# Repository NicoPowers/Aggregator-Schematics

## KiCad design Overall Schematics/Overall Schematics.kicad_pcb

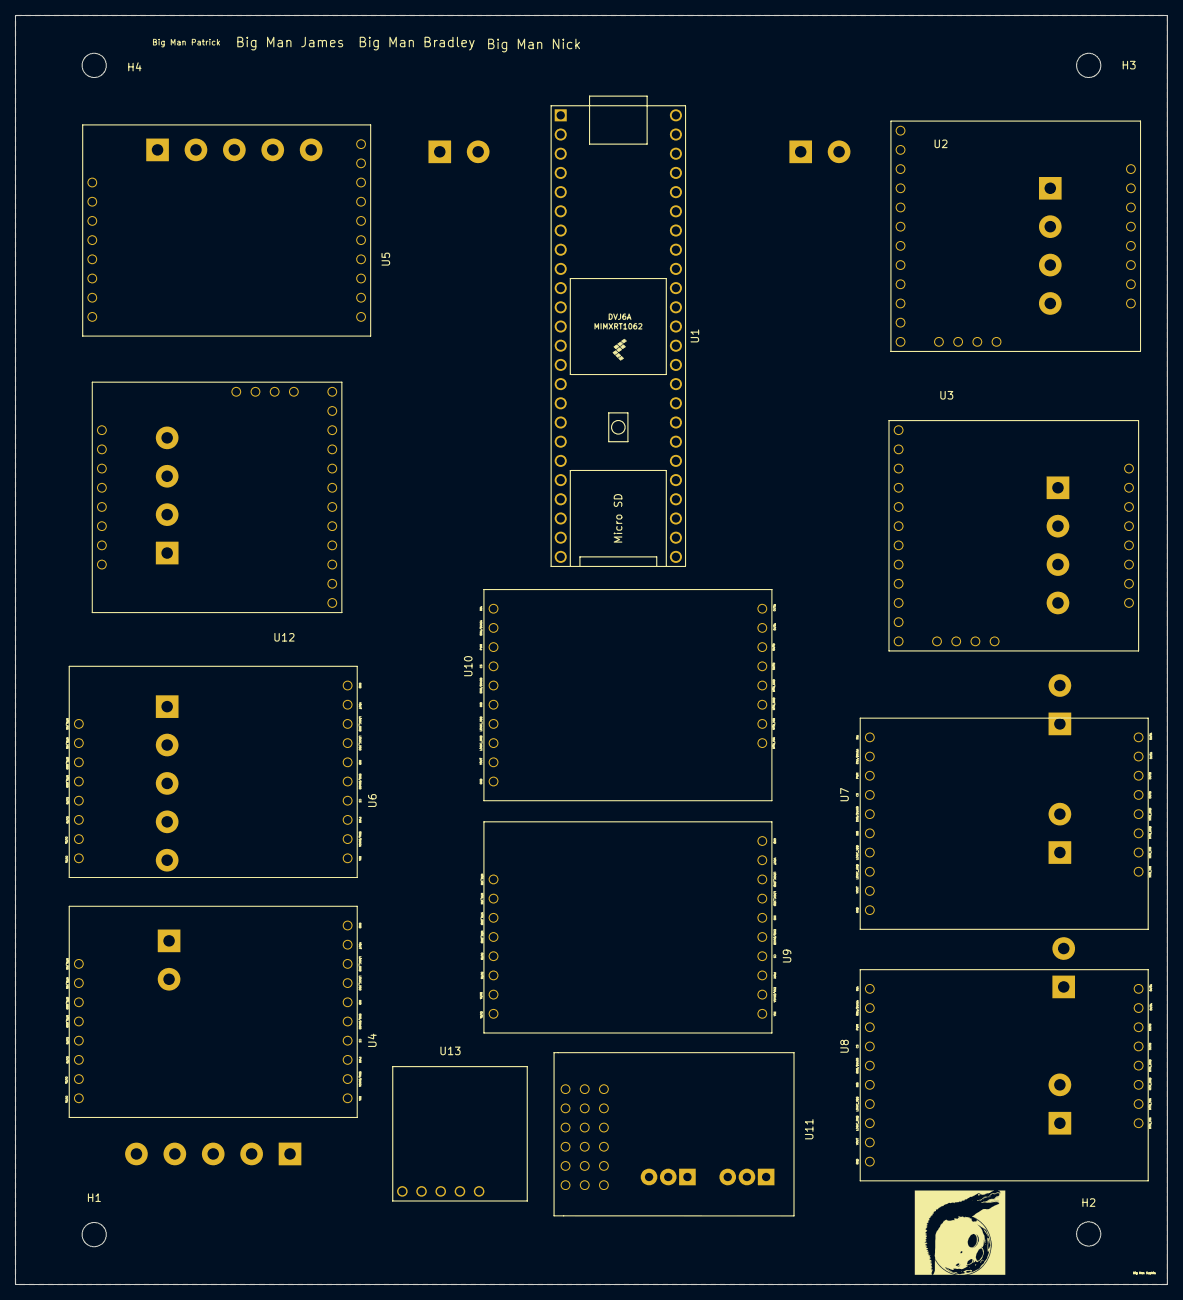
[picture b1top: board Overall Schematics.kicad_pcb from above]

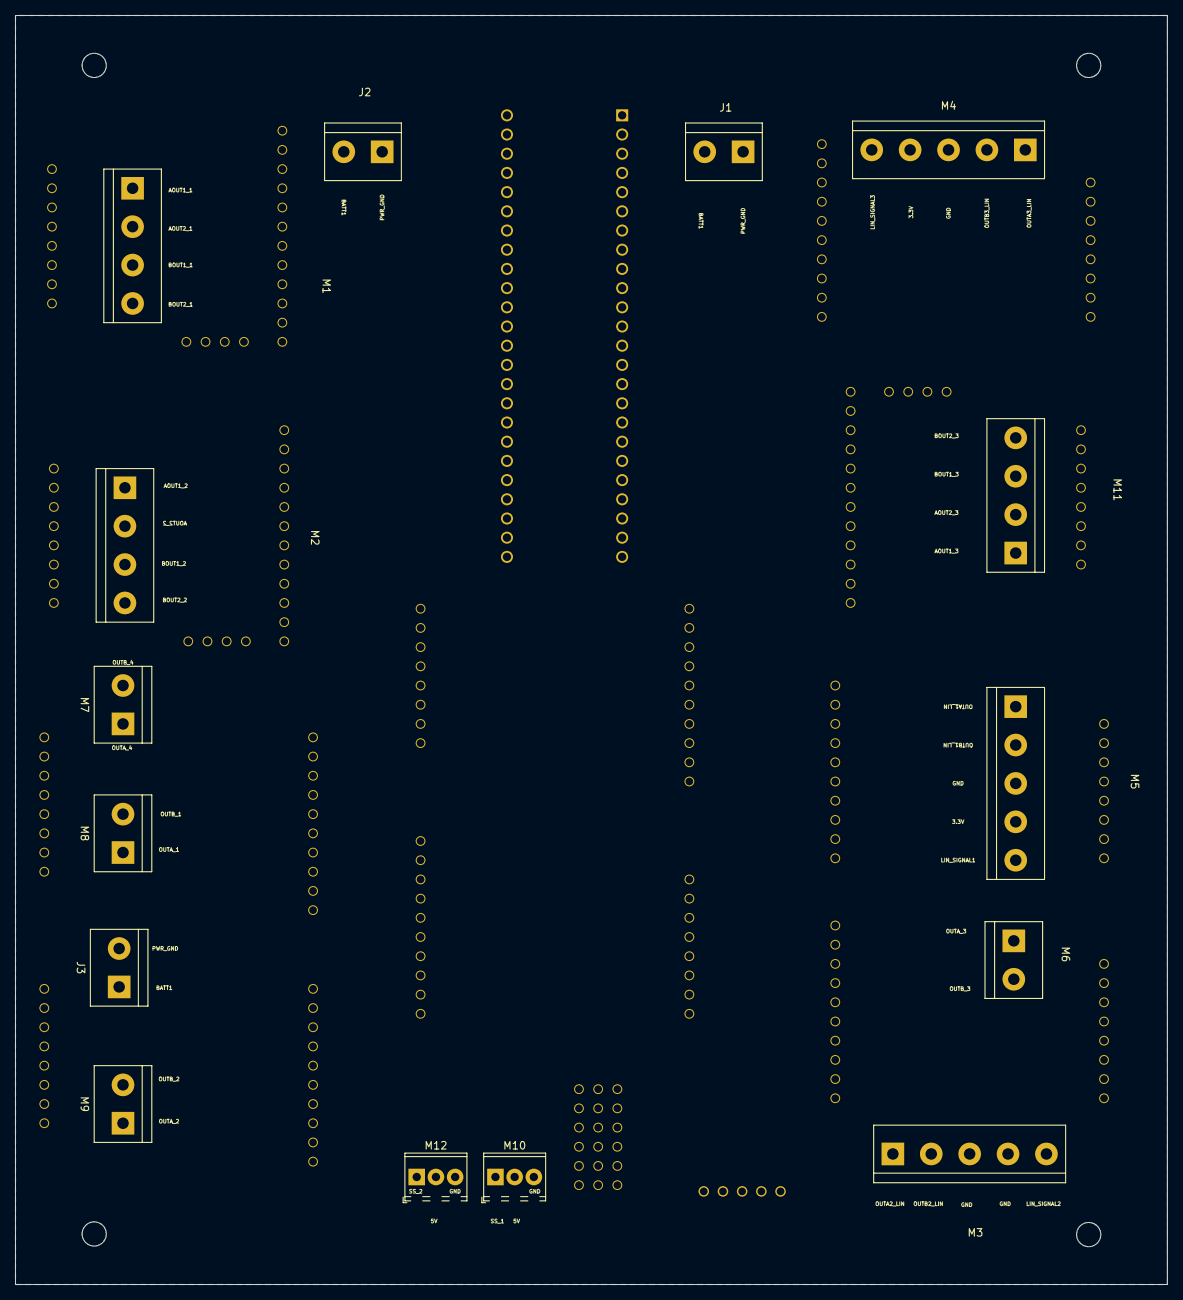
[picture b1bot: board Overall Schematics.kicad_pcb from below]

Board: 2 copper layers, 152.4 x 167.9 mm, 32 parts (15 on the bottom side), 67 nets, no tracks yet.

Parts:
H1, H2, H3, H4: MountingHole; MountingHole_3.2mm_M3
J1: WattMeter1_Output; TerminalBlock_bornier-2_P5.08mm
J2: WattMeter2_Output; TerminalBlock_bornier-2_P5.08mm
J3: Intel_Buck_Converter_Input; TerminalBlock_bornier-2_P5.08mm
M1, M2, M11: Stepper_Motor_bipolar; TerminalBlock_bornier-4_P5.08mm
M3, M4, M5: LinActuator12V; TerminalBlock_bornier-5_P5.08mm
M6, M7, M8, M9: Motor_DC; TerminalBlock_bornier-2_P5.08mm
M10, M12: Motor_Servo; TerminalBlock_2.54_1x03_P2.54mm_Horizontal
U1: Teensy4.1; Teensy41
U2, U3, U12: 36v4SMD; StepperMotorDriver
U4, U5, U6, U7, U8, U9, U10: VNH52019; DCMotorDriver
U11: ServoDriver; ServoMotorDriver
U13: D24V22F5

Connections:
3.3V: M3.4, M4.4, M5.4, U1.46, U4.7, U5.7, U6.7, U7.7, U8.7, U9.7, U10.7
+5V: M10.2, M12.2, U11.7, U11.8, U13.5
AOUT1_1: M1.1, U2.21
AOUT1_2: M2.1, U3.21
AOUT1_3: M11.1, U12.21
AOUT2_1: M1.2, U2.22
AOUT2_2: M2.2, U3.22
AOUT2_3: M11.2, U12.22
BOUT1_1: M1.3, U2.23
BOUT1_2: M2.3, U3.23
BOUT1_3: M11.3, U12.23
BOUT2_1: M1.4, U2.24
BOUT2_2: M2.4, U3.24
BOUT2_3: M11.4, U12.24
Battery1_Positive24V: J1.2, J2.2, J3.1, U2.17, U2.18, U3.17, U3.18, U4.11, U5.14, U6.14, U7.11, U8.11, U9.14, U10.11, U12.17, U12.18, U13.3
DIR_1: U1.44, U2.5
DIR_2: U1.40, U3.5
DIR_3: U1.9, U12.5
GND: M3.3, M4.3, M5.3, M10.3, M12.3, U1.1, U1.34, U1.47, U2.3, U3.3, U4.8, U5.8, U6.8, U7.8, U8.8, U9.8, U10.8, U11.13, U11.14, U12.3, U13.4
INA_1: U1.35, U7.1
INA_2: U1.30, U8.1
INA_3: U1.27, U9.1
INA_4: U1.23, U10.1
INA_5: U1.11, U6.1
INA_6: U1.14, U4.1
INA_7: U1.4, U5.1
INB_1: U1.37, U7.6
INB_2: U1.32, U8.6
INB_3: U1.28, U9.6
INB_4: U1.22, U10.6
INB_5: U1.13, U6.6
INB_6: U1.20, U4.6
INB_7: U1.6, U5.6
LIN_SIGNAL1: M5.5, U1.18
LIN_SIGNAL2: M3.5, U1.19
LIN_SIGNAL3: M4.5, U1.17
OUTA1_LIN: M5.1, U6.11
OUTA2_LIN: M3.1, U4.14
OUTA3_LIN: M4.1, U5.11
OUTA_1: M8.1, U7.14, U10.14
OUTA_2: M9.1, U8.14
OUTA_3: M6.1, U9.11
OUTB1_LIN: M5.2, U6.12
OUTB2_LIN: M3.2, U4.13
OUTB3_LIN: M4.2, U5.12
OUTB_1: M8.2, U7.13
OUTB_2: M9.2, U8.13, U10.13
OUTB_3: M6.2, U9.12
PWM_1: U1.36, U7.3
PWM_2: U1.31, U8.3
PWM_3: U1.29, U9.3
PWM_4: U1.21, U10.3
PWM_5: U1.12, U6.3
PWM_6: U1.16, U4.3
PWM_7: U1.5, U5.3
PWR_GND: J1.1, J2.1, J3.2, U2.19, U2.20, U3.19, U3.20, U4.12, U5.13, U6.13, U7.12, U8.12, U9.13, U10.12, U12.19, U12.20
RESET_1: U1.42, U2.11
RESET_2: U1.38, U3.11
RESET_3: U1.7, U12.11
SLEEP_1: U1.43, U2.10
SLEEP_2: U1.39, U3.10
SLEEP_3: U1.8, U12.10
SS_1: M10.1, U11.1
SS_2: M12.1, U11.2
STEP_1: U1.45, U2.4
STEP_2: U1.41, U3.4
STEP_3: U1.10, U12.4

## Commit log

2020-10-27 added first project
2020-10-27 added motor schematics
2020-10-29 edited some voltage and name of stepper motor
2020-11-01 made some changes
2020-11-03 adding labels to pins
2020-11-03 Ahoy this be the JRK2 model
2020-11-03 made area bigger
2020-11-10 Added Linear Actuators and DC Motor Controller
2020-11-10 Battery Changes
    Added battery terminals, watt meter, and intel buck converter
2021-01-03 adding new footprints
2021-01-10 motor drive footprints completed (ready for pcb)
2021-01-17 beginning of the pcb
2021-01-17 come changes
2021-01-17 started PCB traces, need to add maestro servo board stuff
2021-01-17 fixed stuff
2021-01-20 new symbol
2021-01-20 PCB Schematic update minor
    Minor change
2021-01-24 Revert "PCB Schematic update minor"
    This reverts commit 3e80528f7cd4e1471eff03cf61a2cb16ed800615.
2021-01-24 added 6 in cutout
2021-01-24 placement of ICs and proper pin connectors are pretty much done
2021-01-24 finished routing main ICs, have to figure out power routing, vary track width
2021-01-24 locked some ICs
2021-01-31 flipped some screw terminals and added screw terminal
2021-01-31 footprint for servo controller
2021-01-31 PCB Updates
2021-02-03 pulling
2021-02-03 footprint for buck converter power supply
2021-02-03 did some pcb stuff
2021-02-03 Added 5V buck
2021-02-03 PCB is basically done, going to check stuff again before ordering though
2021-02-03 Added mounting, add to make board a bit bigger. Changed servo screw terminal pitch to 2.54mm
2021-02-04 added the silkscreens
2021-02-07 very important changes
2021-02-07 Added Logo!
2021-02-08 fixed mounting hole locations
2021-02-08 Revert "Added Logo!"
    This reverts commit 306d61a4012bfa4b7f7acb0c31bda849dee03618.
2021-02-09 made silkscreens on back
2021-02-10 movied slightly
2021-02-10 Track Width Changes
2021-02-10 Moved silkscreens
2021-02-10 small changes
2021-02-21 Added Logo
2021-02-21 Added Gerberfiles
2021-02-22 added small adjustments
2021-02-24 gerber 2 added
2022-02-28 Beginning Design fixes
2022-02-28 Changing VNH5019 layout to match physical
